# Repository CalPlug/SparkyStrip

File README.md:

# SparkyStrip
**************************************
This is an EECS senior design for Electrical Engineering and Computer Science depatment at UC Irvine for 2015

Coding Development by: Jeffrey Thompson, Andrew Picard, David Pynes, and Edmund Loo

Managed by: Linyi Xia and Prof. G.P. Li

California Plug Load Research Center (CalPlug), California Institute of Telecommunications and Information Technology (Calit2), University of California, Irvine extending from a project in collaboration with The University of California, Davis.

Copyright (c) Regents of the University of California, 2015

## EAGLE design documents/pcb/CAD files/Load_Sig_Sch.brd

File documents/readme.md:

# Sparky Strip Project Documentation

************************************************************
************************************************************

Planning documents and project files for the SparkyStrip Project

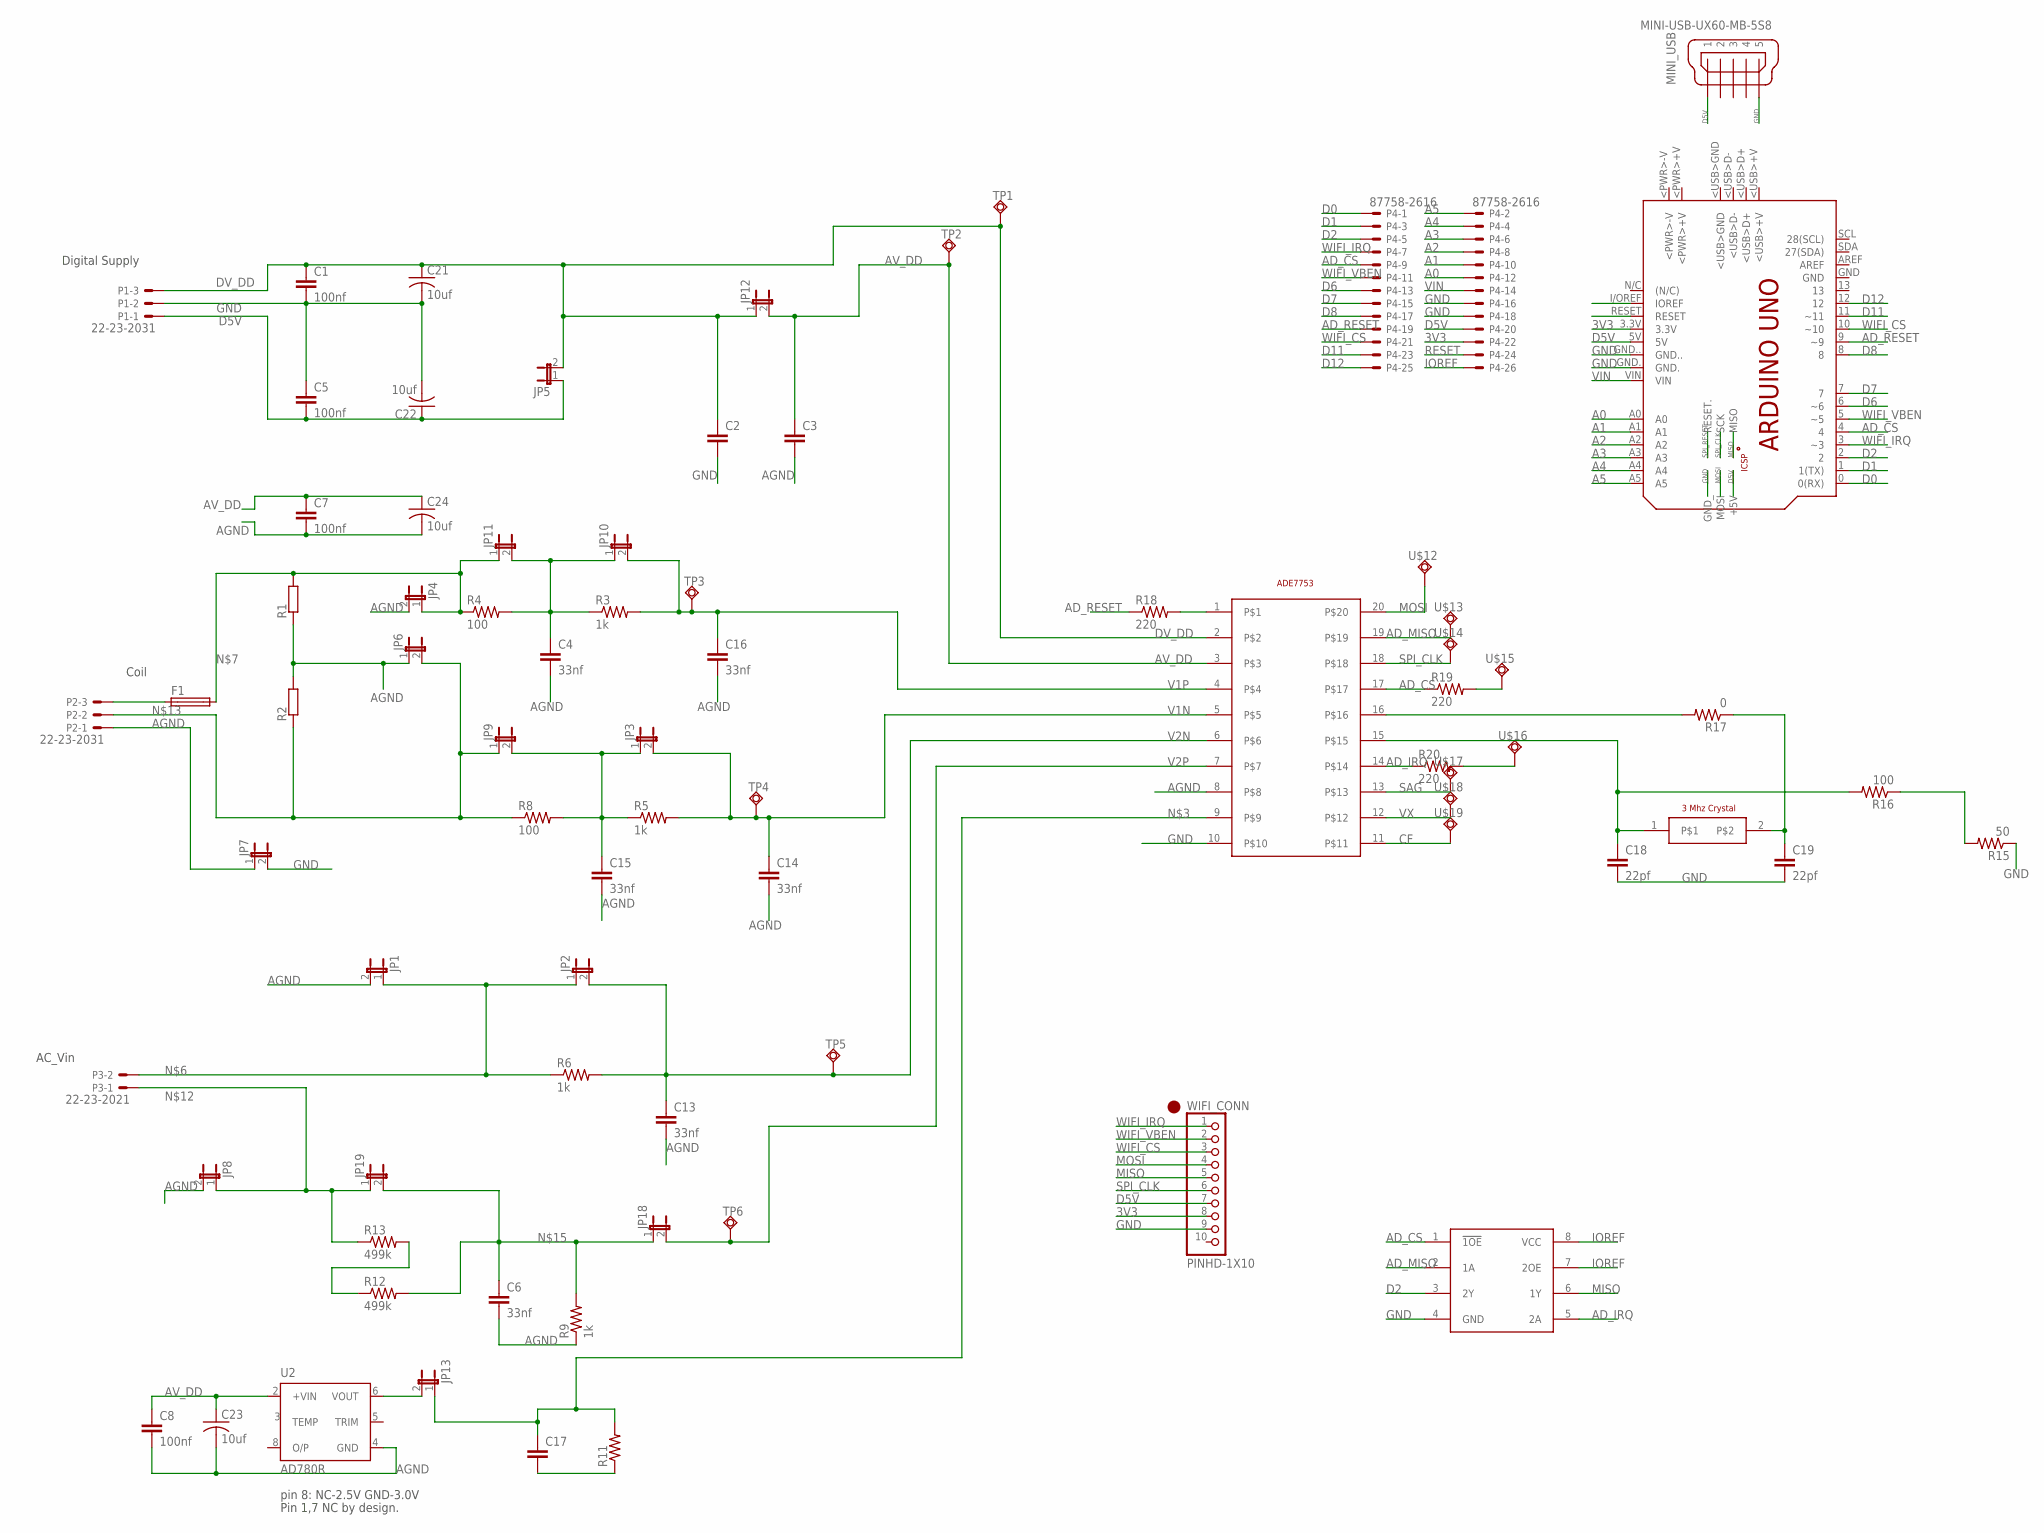
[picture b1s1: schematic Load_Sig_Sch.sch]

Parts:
C1, C5, C7, C8: 100nf; C025-024X044
C2, C3, C17: C-EU025-024X044; C025-024X044
C4, C6, C13, C14, C15, C16: 33nf; C025-024X044
C18, C19: 22pf; C025-024X044
C21, C22, C23, C24: 10uf; C025-024X044
F1: 19560
JP1, JP2, JP3, JP4, JP5, JP6, JP7, JP8, JP9, JP10, JP11, JP12, JP13, JP18, JP19: JP1E; JP1
MINI_USB: MINI-USB-UX60-MB-5S8; UX60-MB-5S8
P1, P2: 22-23-2031
P3: 22-23-2021
P4: 87758-2616
PCB1: ARDUINO_UNO
R1, R2: BVS
R3, R5, R6, R9: 1k; 0204V
R4, R8, R16: 100; 0204V
R11: R-US_0204/2V; 0204V
R12, R13: 499k; 0204V
R15: 50; 0204V
R17: 0; 0204V
R18, R19, R20: 220; 0603-RES
TP1, TP2, TP3, TP4, TP5, TP6: TEST
U1: ADE7753; SSOP20
U2: AD780R; SO8
U3: 74LVC2G241; SOP65P490X110-8N
U$2: X079-ND_CRYSTAL; HC49US
U$12, U$13, U$14, U$15, U$16, U$17, U$18, U$19: TEST
WIFI_CONN: PINHD-1X10; 1X10-BIG

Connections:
3V3: P4.22, PCB1.3.3V, WIFI_CONN.8
A0: P4.12, PCB1.A0
A1: P4.10, PCB1.A1
A2: P4.8, PCB1.A2
A3: P4.6, PCB1.A3
A4: P4.4, PCB1.A4
A5: P4.2, PCB1.A5
AD_CS: P4.9, PCB1.4, R19.1, U1.17, U3.1 (!1OE)
AD_IRQ: R20.1, U1.14, U3.5 (2A)
AD_MISO: U1.19, U3.2 (1A), U$13.1
AD_RESET: P4.19, PCB1.9 (~9), R18.1
AGND: C3.2, C4.2, C6.2, C7.2, C8.2, C13.2, C14.2, C15.2, C16.2, C23.2, C24.2, JP1.2, JP4.2, JP6.1, JP7.1, JP8.2, P2.1, R1.2, R2.1, R9.1, U1.8, U2.4 (GND)
AV_DD: C3.1, C7.1, C8.1, C23.1, C24.1, JP12.2, TP2.1, U1.3, U2.2 (+VIN)
CF: U1.11, U$19.1
D0: P4.1, PCB1.0 (0(RX))
D1: P4.3, PCB1.1 (1(TX))
D2: P4.5, PCB1.2, U3.3 (2Y)
D5V: C5.2, C22.1, JP5.1, MINI_USB.1, P1.1, P4.20, PCB1.5V, PCB1.+5V, WIFI_CONN.7
D6: P4.13, PCB1.6 (~6)
D7: P4.15, PCB1.7
D8: P4.17, PCB1.8
D11: P4.23, PCB1.11 (~11)
D12: P4.25, PCB1.12
DV_DD: C1.1, C2.1, C21.1, JP5.2, JP12.1, P1.3, TP1.1, U1.2
GND: C1.2, C2.2, C5.1, C18.2, C19.2, C21.2, C22.2, JP7.2, MINI_USB.5, P1.2, P4.16, P4.18, PCB1.GND., PCB1.GND.., PCB1.GND_, R15.1, U1.10, U3.4 (GND), WIFI_CONN.9
IOREF: P4.26, PCB1.I/OREF (IOREF), U3.7 (2OE), U3.8 (VCC)
MISO: PCB1.MISO, U3.6 (1Y), WIFI_CONN.5
MOSI: PCB1.MOSI, U1.20, U$12.1, WIFI_CONN.4
unnamed: F1.1, P2.3
unnamed: C17.1, JP13.1, R11.2, U1.9
unnamed: C18.1, R16.2, U1.15, U$2.1
unnamed: C19.1, R17.1, U$2.2
unnamed: JP1.1, JP2.1, P3.2, R6.1
unnamed: F1.2, JP4.1, JP11.1, R1.1, R4.1
unnamed: C4.1, JP10.1, JP11.2, R3.1, R4.2
unnamed: R15.2, R16.1
unnamed: C15.1, JP3.1, JP9.2, R5.1, R8.2
unnamed: JP8.1, JP19.1, P3.1, R13.1
unnamed: JP6.2, JP9.1, P2.2, R2.2, R8.1
unnamed: R17.2, U1.16
unnamed: C6.1, JP18.1, JP19.2, R9.2, R12.2
unnamed: R12.1, R13.2
unnamed: JP13.2, U2.6 (VOUT)
unnamed: C17.2, R11.1
unnamed: R19.2, U$15.1
unnamed: R20.2, U$16.1
RESET: P4.24, PCB1.RESET
RESETBIN: R18.2, U1.1
SAG: U1.13, U$17.1
SPI_CLK: PCB1.SCK, U1.18, U$14.1, WIFI_CONN.6
SPI_RESET: PCB1.RESET.
V1N: C14.1, JP3.2, R5.2, TP4.1, U1.5
V1P: C16.1, JP10.2, R3.2, TP3.1, U1.4
V2N: C13.1, JP2.2, R6.2, TP5.1, U1.6
V2P: JP18.2, TP6.1, U1.7
VIN: P4.14, PCB1.VIN
VX: U1.12, U$18.1
WIFI_CS: P4.21, PCB1.10 (~10), WIFI_CONN.3
WIFI_IRQ: P4.7, PCB1.3 (~3), WIFI_CONN.1
WIFI_VBEN: P4.11, PCB1.5 (~5), WIFI_CONN.2

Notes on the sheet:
Coil
Digital Supply
AC_Vin
pin 8: NC-2.5V GND-3.0V
Pin 1,7 NC by design.

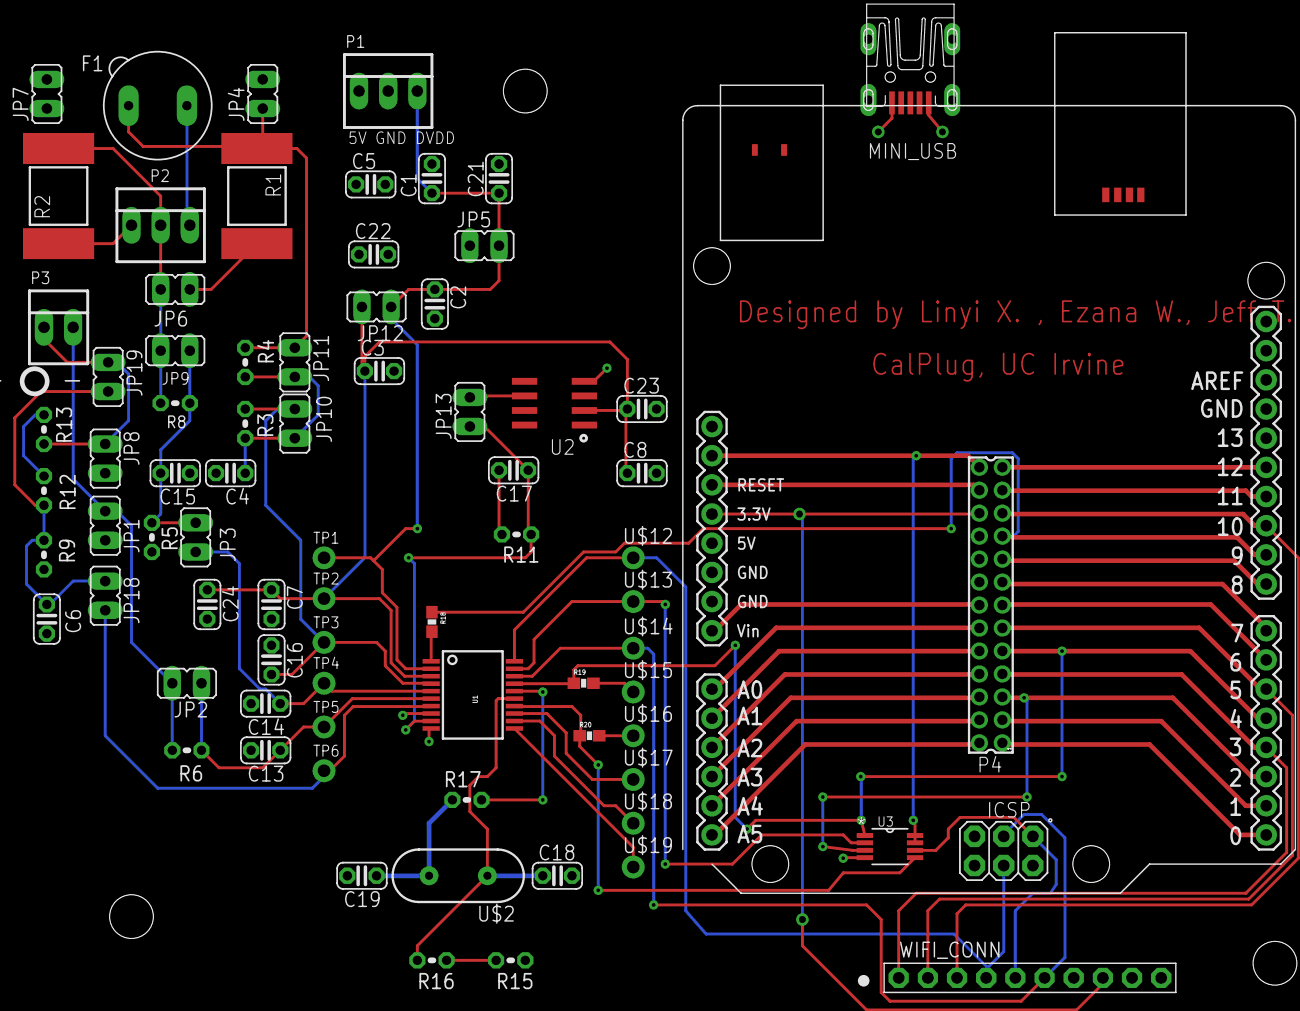
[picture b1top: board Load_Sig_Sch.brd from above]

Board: 4 copper layers, 77 parts (0 on the bottom side), 59 nets.

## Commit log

2017-11-07 Initial project upload
    Initial project upload

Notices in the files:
parts and their libraries:
SparkFun-Passives: Licensing: Creative Commons ShareAlike 4.0 International - https://creativecommons.org/licenses/by-sa/4.0
